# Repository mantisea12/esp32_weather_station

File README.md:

# ESP32 Weather Station

A compact 2-layer weather monitoring system based on the ESP32, designed to measure and display environmental conditions.

## Features

- ESP32 microcontroller
- BME680 environmental sensor
- DHT11 temperature and humidity sensor
- OLED display interface
- Battery-powered operation
- USB programming and power input
- On-board voltage regulation

## Measurements

The system is capable of monitoring:

- Temperature
- Relative humidity
- Atmospheric pressure
- Air quality (VOC/gas resistance)
- Estimated altitude

## Design Information

- PCB Layers: 2
- Software: KiCad
- MCU: ESP32

## Repository Contents

- KiCad project files
- Manufacturing Gerbers
- Bill of Materials (BOM)
- PCB renders and screenshots

## Notes

This was my first PCB design project and was created to learn PCB layout, power distribution, sensor interfacing, and embedded hardware design.

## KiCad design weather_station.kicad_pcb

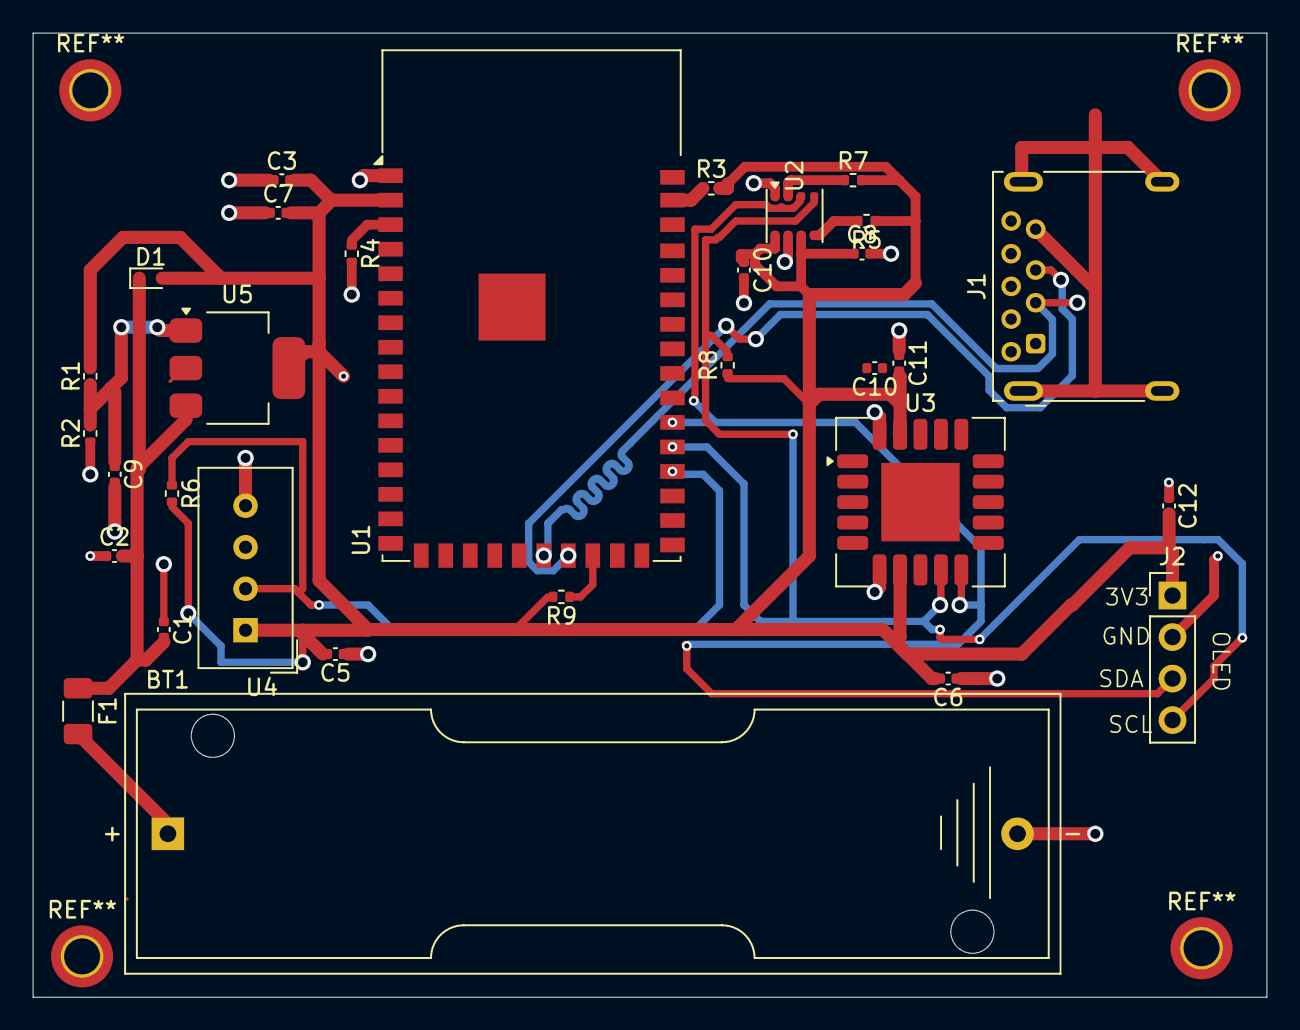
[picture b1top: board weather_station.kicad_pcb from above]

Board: 2 copper layers, 75.5 x 59.0 mm, 32 parts (1 on the bottom side), 15 nets.

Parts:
BT1: Battery; BatteryHolder_Keystone_2460_1xAA
C1, C5, C6, C7, C8, C10, C10#2, C11, C12: 100n; C_0402_1005Metric
C2, C3, C9: 10u; C_0402_1005Metric
C4: 22u; C_Elec_3x5.4
D1: 1N914WT; D_SOD-523
F1: 1a; Fuse_1206_3216Metric
J1: USB_A; USB3_A_Molex_48393-001
J2: Conn_01x04; PinHeader_1x04_P2.54mm_Vertical
R1: 360; R_0402_1005Metric
R2: 220; R_0402_1005Metric
R3, R4, R5, R7: 10k; R_0402_1005Metric
R6, R8, R9: 4.7k; R_0402_1005Metric
U1: ESP32-S2-WROVER-I; ESP32-S2-WROVER
U2: BME680; Bosch_LGA-8_3x3mm_P0.8mm_ClockwisePinNumbering
U3: SCD40-D-R2; Sensirion_SCD4x-1EP_10.1x10.1mm_P1.25mm_EP4.8x4.8mm
U4: DHT11; Aosong_DHT11_5.5x12.0_P2.54mm
U5: AMS1117; SOT-223-3_TabPin2

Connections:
GND: BT1.2 (-), C1.1, C2.1, C3.1, C4.2, C5.1, C6.1, C7.1, C8.2, C9.2, C10#2.1, C11.1, C12.1, J1.4 (GND), J1.SH (Shield), J2.2, R2.1, R4.2, U2.1 (GND), U3.6 (GND), U3.20 (GND), U3.21 (GND), U4.4 (GND)
unnamed: BT1.1 (+), F1.2
unnamed: C3.2, C4.1, C5.2, C6.2, C7.2, C8.1, C10.1, C10#2.2, C11.2, C12.2, D1.2 (A), J2.1, R1.2, R3.2, R5.1, R6.2, R7.2, R8.1, R9.2, U1.2 (3V3), U2.6 (VDDIO), U2.8 (VDD), U3.7 (VDD), U3.19 (VDD), U4.1 (VDD), U5.2 (VO)
unnamed: C1.2, C2.2, D1.1 (K), F1.1, U5.3 (VI)
unnamed: J1.3 (D+), U1.23 (USB_D+)
unnamed: J1.2 (D-), U1.22 (USB_D-)
unnamed: J2.3, R9.1, U1.32 (IO38), U2.3 (SDI), U3.10 (SDA)
unnamed: J2.4, R8.2, U1.31 (IO37), U2.4 (SCK), U3.9 (SCL)
unnamed: R3.1, U1.41 (EN)
unnamed: U1.1 (GND), U1.26 (GND), U1.42 (GND), U1.43 (GND)
unnamed: R4.1, U1.3 (IO00)
unnamed: R6.1, U1.30 (IO36), U4.2 (DATA)
unnamed: R7.1, U2.2 (CSB)
unnamed: R5.2, U2.5 (SDO)
unnamed: C9.1, R1.1, R2.2, U5.1 (ADJ)

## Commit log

2026-06-27 Added files
